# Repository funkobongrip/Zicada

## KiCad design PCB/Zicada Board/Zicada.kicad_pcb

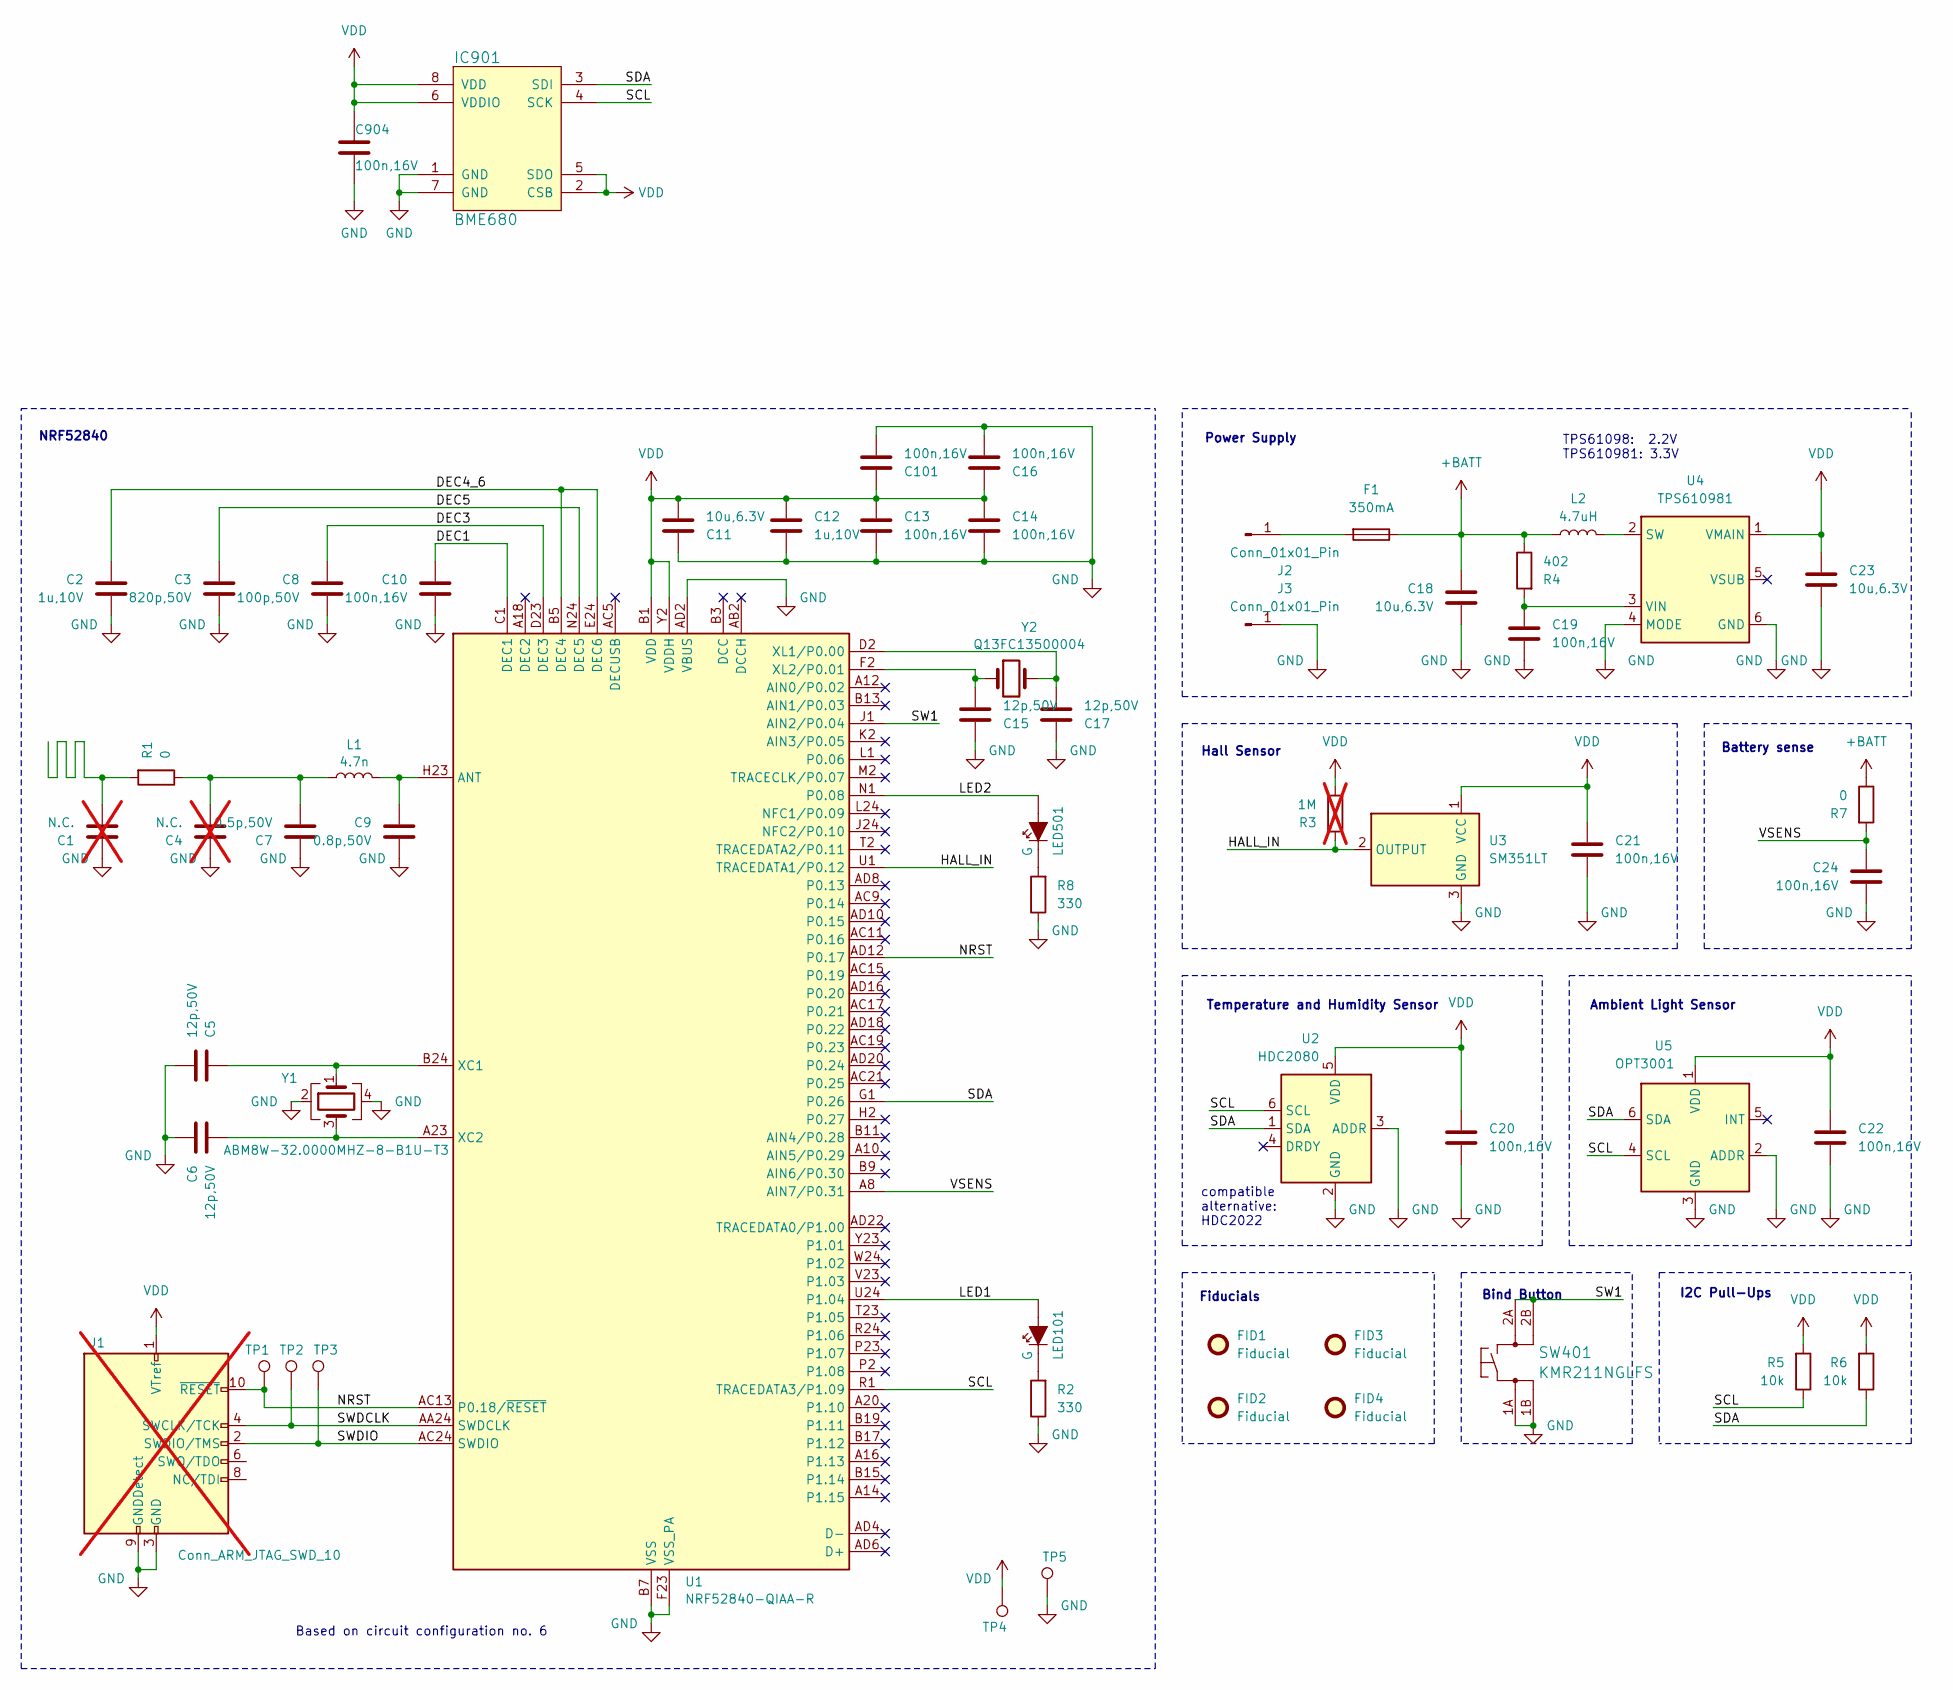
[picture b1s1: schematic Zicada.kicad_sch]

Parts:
C1, C4: N.C.; C0402; not fitted
C2, C12: 1u,10V; C0402
C3: 820p,50V; C0402
C5, C6, C15, C17: 12p,50V; C0402
C7: 0.5p,50V; C0402
C8: 100p,50V; C0402
C9: 0.8p,50V; C0402
C10, C13, C14, C16, C19, C20, C21, C22, C24, C101, C904: 100n,16V; C0402
C11, C18, C23: 10u,6.3V; C0603
F1: 350mA; Fuse_0805_2012Metric; LCSC C207021
FID1, FID2, FID3, FID4: Fiducial; FIDUCIAL_1mm
IC901: BME680
J1: Conn_ARM_JTAG_SWD_10; TC2050-IDC-NLFP; not fitted
J2, J3: Conn_01x01_Pin; MYOUNG MY-AAA-07; LCSC C6937109
L1: 4.7n; L0402
L2: 4.7uH; L_1008_2520Metric; LCSC C280597
LED101, LED501: G; LED0603
R1, R7: 0; R0402
R2, R8: 330; R0402
R3: 1M; R0402; not fitted
R4: 402; R0603; LCSC C227889
R5, R6: 10k; R0402
SW401: KMR211NGLFS; TACT_SW4_KMR2
TP1, TP2, TP3, TP4, TP5: TestPoint; TestPoint_Pad_D1.5mm
U1: NRF52840-QIAA-R; Nordic_AQFN-73-1EP_7x7mm_P0.5mm; LCSC C190794
U2: HDC2080; Texas_PWSON-N6; LCSC C918141
U3: SM351LT; SOT-23; LCSC C80830
U4: TPS610981; WSON-6_1.5x1.5mm_P0.5mm; LCSC C470966
U5: OPT3001; USON-6-1EP_2x2mm_P0.65mm_EP0.65x1.35mm; LCSC C90462
Y1: ABM8W-32.0000MHZ-8-B1U-T3; Crystal_SMD_Abracon_ABM8G-4Pin_3.2x2.5mm; LCSC C5552502
Y2: Q13FC13500004; Crystal_SMD_MicroCrystal_CC7V-T1A-2Pin_3.2x1.5mm; LCSC C32346

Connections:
+BATT: C18.1, F1.1, L2.1, R4.1, R7.1
/DEC1: C10.1, U1.C1 (DEC1)
/DEC3: C8.1, U1.D23 (DEC3)
/DEC4_6: C2.1, U1.B5 (DEC4), U1.E24 (DEC6)
/DEC5: C3.1, U1.N24 (DEC5)
/HALL_IN: R3.2, U1.U1 (TRACEDATA1/P0.12), U3.2 (OUTPUT)
/LED1: LED101.A, U1.U24 (P1.04)
/LED2: LED501.A, U1.N1 (P0.08)
/NRST: J1.10 (~RESET), TP1.1 (1_1), U1.AC13 (P0.18/~RESET), U1.AD12 (P0.17)
/SCL: IC901.4 (SCK), R5.1, U1.R1 (TRACEDATA3/P1.09), U2.6 (SCL), U5.4 (SCL)
/SDA: IC901.3 (SDI), R6.1, U1.G1 (P0.26), U2.1 (SDA), U5.6 (SDA)
/SW1: SW401.2A, SW401.2B, U1.J1 (AIN2/P0.04)
/SWDCLK: J1.4 (SWCLK/TCK), TP2.1 (1_1), U1.AA24 (SWDCLK)
/SWDIO: J1.2 (SWDIO/TMS), TP3.1 (1_1), U1.AC24 (SWDIO)
/VSENS: C24.1, R7.2, U1.A8 (AIN7/P0.31)
GND: C1.1, C2.2, C3.2, C4.1, C5.2, C6.1, C7.1, C8.2, C9.2, C10.2, C11.1, C12.2, C13.2, C14.2, C15.1, C16.2, C17.1, C18.2, C19.2, C20.2, C21.2, C22.2, C23.2, C24.2, C101.2, C904.2, IC901.1 (GND), IC901.7 (GND), J1.3 (GND), J1.5 (GND), J1.9 (GNDDetect), J3.1 (Pin_1_1), R2.1, R8.1, SW401.1A, SW401.1B, TP5.1 (1_1), U1.AD2 (VBUS), U1.B7 (VSS), U1.EP (VSS), U1.F23 (VSS_PA), U2.2 (GND), U2.3 (ADDR), U3.3 (GND), U4.4 (MODE), U4.6 (GND), U5.2 (ADDR), U5.3 (GND), Y1.2, Y1.4
unnamed: C1.2, R1.2
unnamed: C4.2, C7.2, L1.1, R1.1
unnamed: F1.2, J2.1 (Pin_1_1)
unnamed: LED101.C, R2.2
unnamed: LED501.C, R8.2
unnamed: C9.1, L1.2, U1.H23 (ANT)
unnamed: C5.1, U1.B24 (XC1), Y1.1
unnamed: C6.2, U1.A23 (XC2), Y1.3
unnamed: C17.2, U1.D2 (XL1/P0.00), Y2.2
unnamed: C15.2, U1.F2 (XL2/P0.01), Y2.1
unnamed: L2.2, U4.2 (SW)
unnamed: C19.1, R4.2, U4.3 (VIN)
VDD: C11.2, C12.1, C13.1, C14.1, C16.1, C20.1, C21.1, C22.1, C23.1, C101.1, C904.1, IC901.2 (CSB), IC901.5 (SDO), IC901.6 (VDDIO), IC901.8 (VDD), J1.1 (VTref), R3.1, R5.2, R6.2, TP4.1 (1_1), U1.A22 (VDD), U1.AD14 (VDD), U1.AD23 (VDD), U1.B1 (VDD), U1.W1 (VDD), U1.Y2 (VDDH), U2.5 (VDD), U3.1 (VCC), U4.1 (VMAIN), U5.1 (VDD)

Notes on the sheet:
NRF52840
Ambient Light Sensor
Temperature and Humidity Sensor
Based on circuit configuration no. 6
compatible alternative: HDC2022
Bind Button
Power Supply
TPS61098: 2.2V TPS610981: 3.3V
Fiducials
Battery sense
I2C Pull-Ups
Hall Sensor

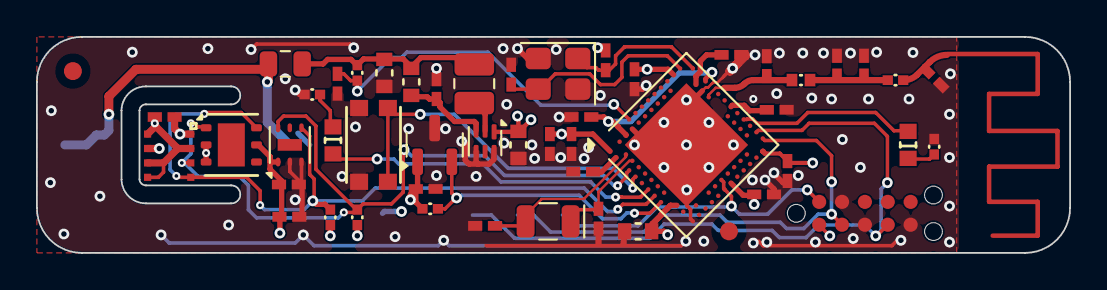
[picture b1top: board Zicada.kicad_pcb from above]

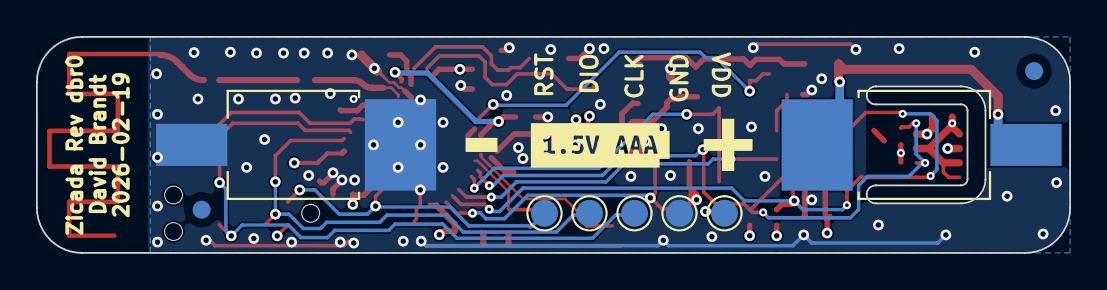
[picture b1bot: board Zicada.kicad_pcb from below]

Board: 4 copper layers, 57.4 x 12.0 mm, 63 parts (12 on the bottom side), 29 nets.

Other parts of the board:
kibuzzard-6898F1CE: G***; kibuzzard-6898F1CE
kibuzzard-6898F6DD: G***; kibuzzard-6898F6DD
kibuzzard-6898F105: G***; kibuzzard-6898F105

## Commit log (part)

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2026-02-19 Everything 0402, 4 layer board
2026-02-19 Add BME688
